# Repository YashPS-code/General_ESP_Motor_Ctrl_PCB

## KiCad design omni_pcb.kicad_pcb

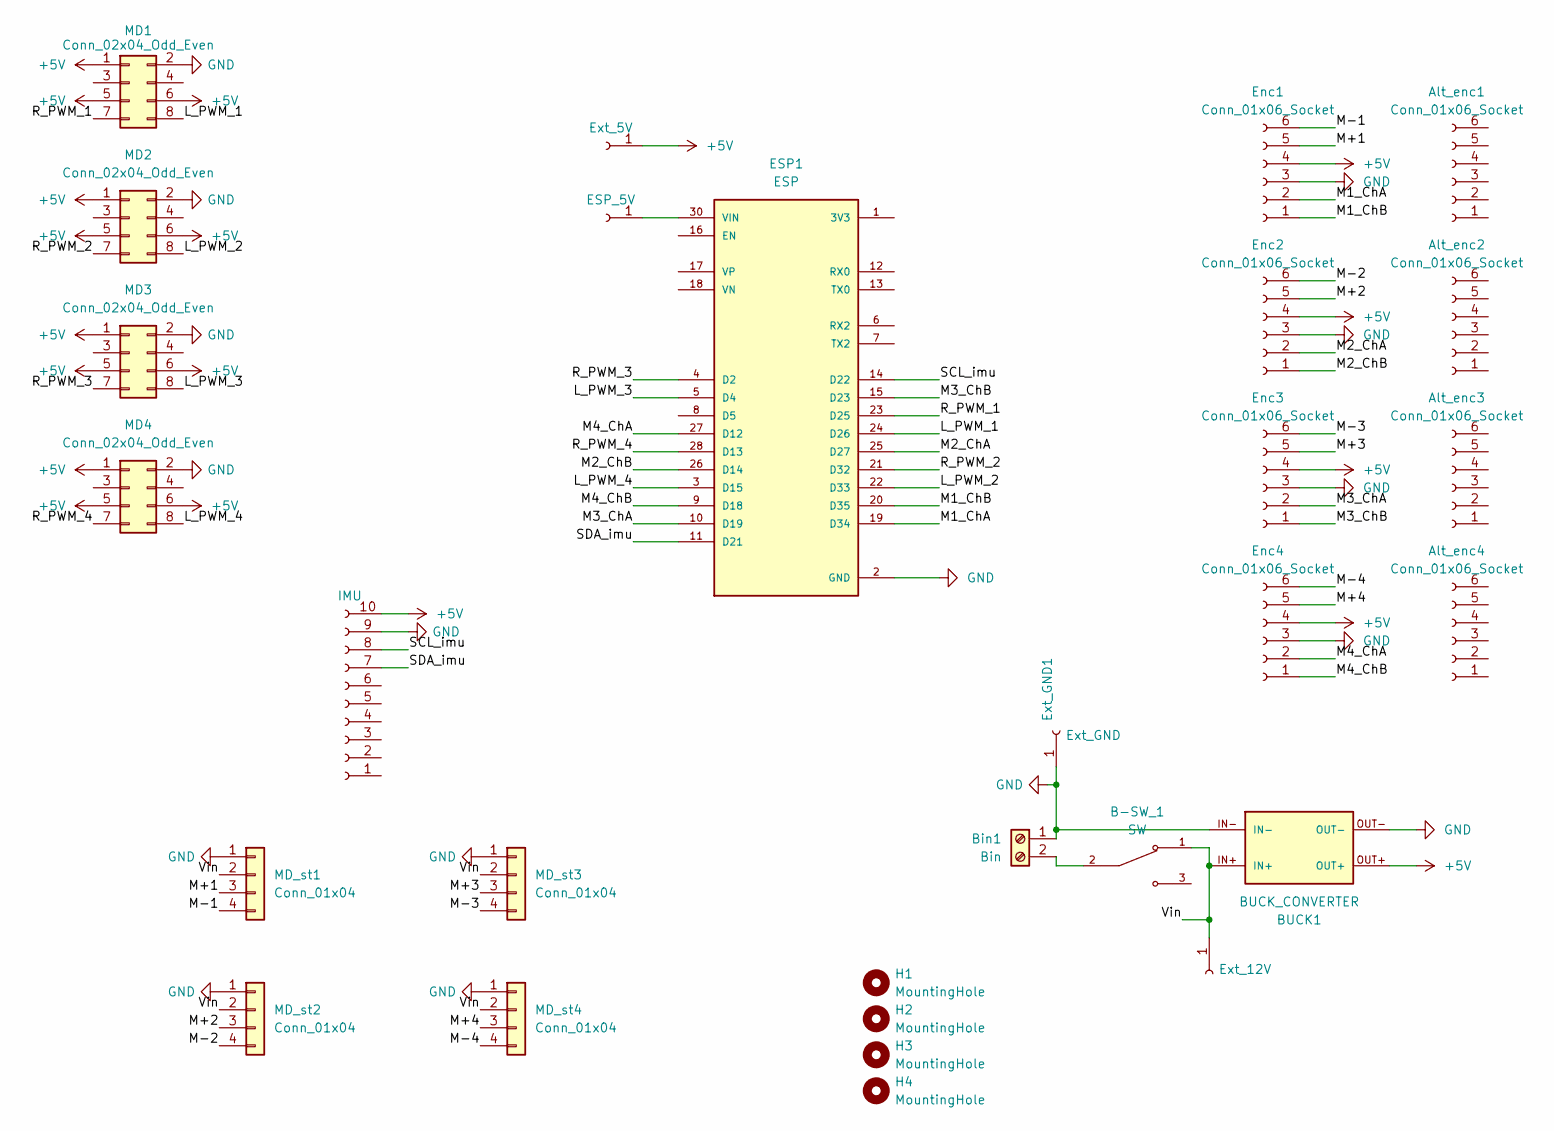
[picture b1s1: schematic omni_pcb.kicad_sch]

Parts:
Alt_enc1, Alt_enc2, Alt_enc3, Alt_enc4: Conn_01x06_Socket; JST_XH_B6B-XH-A_1x06_P2.50mm_Vertical
B-SW_1: SW; SW_100SP1T1B4M2QE; PARTREV E
BUCK1: BUCK_CONVERTER; BUCK_CONVERTER_XL4015E1
Bin1: Bin; TerminalBlock_Xinya_XY308-2.54-2P_1x02_P2.54mm_Horizontal
ESP1: ESP; MODULE_ESP32_DEVKIT_V1; PARTREV N/A
ESP_5V1: ESP_5V; SolderWirePad_1x01_SMD_2x4mm
Enc1, Enc2, Enc3, Enc4: Conn_01x06_Socket; JST_XH_B6B-XH-A_1x06_P2.50mm_Vertical
Ext_5V1: Ext_5V; SolderWirePad_1x01_SMD_2x4mm
Ext_12V1: Ext_12V; SolderWirePad_1x01_SMD_3x6mm
Ext_GND1: Ext_GND; SolderWirePad_1x01_SMD_3x6mm
H1, H2, H3, H4: MountingHole; MountingHole_2.5mm
IMU1: IMU; PinSocket_1x10_P2.54mm_Vertical
MD1, MD2, MD3, MD4: Conn_02x04_Odd_Even; PinSocket_2x04_P2.54mm_Vertical
MD_st1, MD_st2, MD_st3, MD_st4: Conn_01x04; JST_XH_B4B-XH-A_1x04_P2.50mm_Vertical

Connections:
+5V: BUCK1.OUT+, Enc1.4, Enc2.4, Enc3.4, Enc4.4, Ext_5V1.1, IMU1.10, MD1.1, MD1.5, MD1.6, MD2.1, MD2.5, MD2.6, MD3.1, MD3.5, MD3.6, MD4.1, MD4.5, MD4.6
/L_PWM_1: ESP1.24 (D26), MD1.8
/L_PWM_2: ESP1.22 (D33), MD2.8
/L_PWM_3: ESP1.5 (D4), MD3.8
/L_PWM_4: ESP1.3 (D15), MD4.8
/M1_ChA: ESP1.19 (D34), Enc1.2
/M1_ChB: ESP1.20 (D35), Enc1.1
/M2_ChA: ESP1.25 (D27), Enc2.2
/M2_ChB: ESP1.26 (D14), Enc2.1
/M3_ChA: ESP1.10 (D19), Enc3.2
/M3_ChB: ESP1.15 (D23), Enc3.1
/M4_ChA: ESP1.27 (D12), Enc4.2
/M4_ChB: ESP1.9 (D18), Enc4.1
/M+1: Enc1.5, MD_st1.3
/M+2: Enc2.5, MD_st2.3
/M+3: Enc3.5, MD_st3.3
/M+4: Enc4.5, MD_st4.3
/M-1: Enc1.6, MD_st1.4
/M-2: Enc2.6, MD_st2.4
/M-3: Enc3.6, MD_st3.4
/M-4: Enc4.6, MD_st4.4
/R_PWM_1: ESP1.23 (D25), MD1.7
/R_PWM_2: ESP1.21 (D32), MD2.7
/R_PWM_3: ESP1.4 (D2), MD3.7
/R_PWM_4: ESP1.28 (D13), MD4.7
/SCL_imu: ESP1.14 (D22), IMU1.8
/SDA_imu: ESP1.11 (D21), IMU1.7
/Vin: B-SW_1.1, BUCK1.IN+, Ext_12V1.1, MD_st1.2, MD_st2.2, MD_st3.2, MD_st4.2
GND: BUCK1.IN-, BUCK1.OUT-, Bin1.1, ESP1.2 (GND), ESP1.29 (GND), Enc1.3, Enc2.3, Enc3.3, Enc4.3, Ext_GND1.1, IMU1.9, MD1.2, MD2.2, MD3.2, MD4.2, MD_st1.1, MD_st2.1, MD_st3.1, MD_st4.1
unnamed: B-SW_1.2, Bin1.2
unnamed: ESP1.30 (VIN), ESP_5V1.1

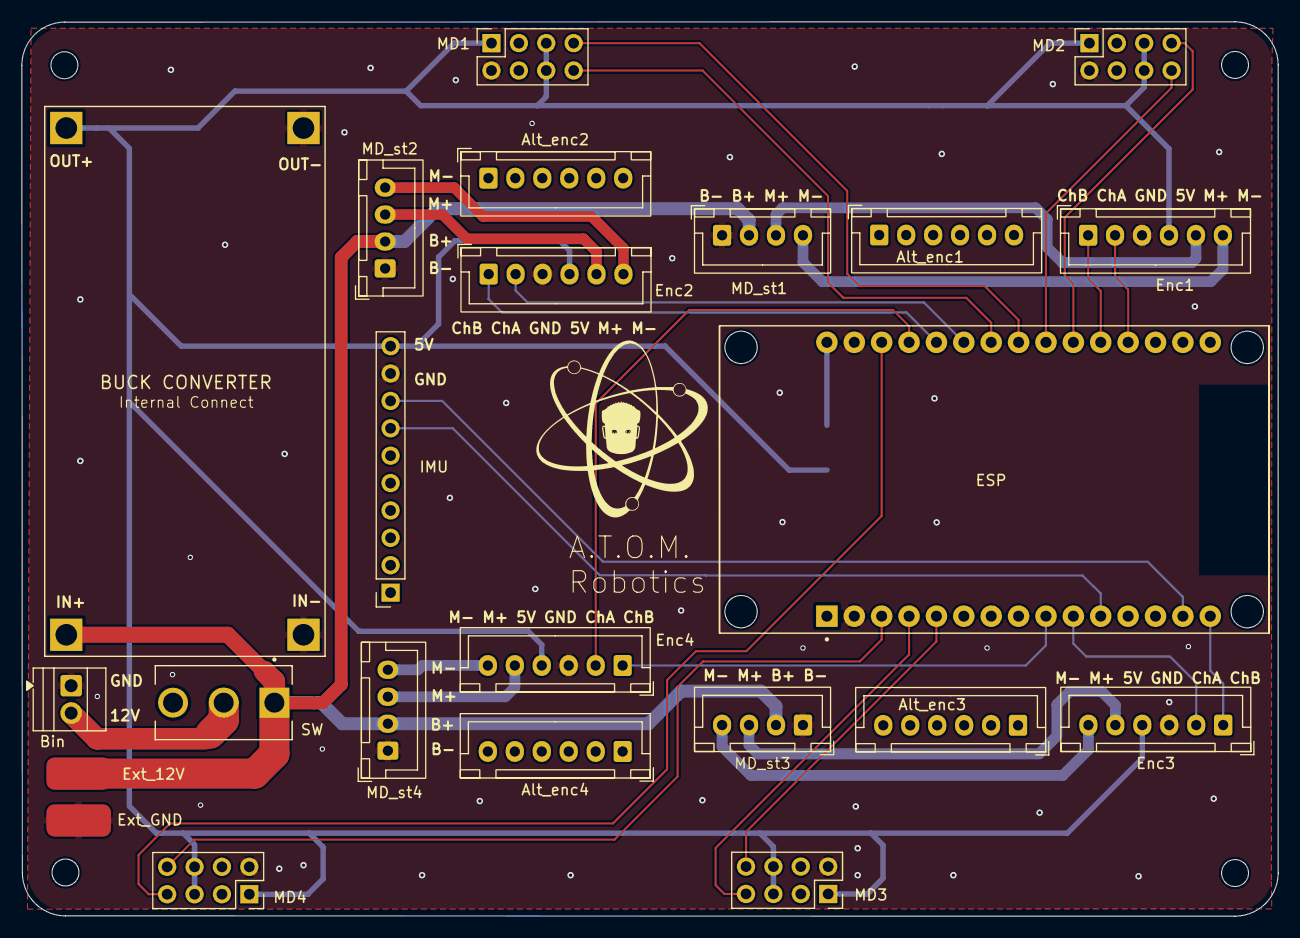
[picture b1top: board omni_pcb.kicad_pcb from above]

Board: 2 copper layers, 116.5 x 82.9 mm, 30 parts (0 on the bottom side), 31 nets.

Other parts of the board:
atom: LOGO; atom_logo_20x20mm

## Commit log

2026-04-13 PCB layout
2026-04-13 Remove unwanted file
2026-05-07 traces
2026-05-08 pcb final
2026-05-09 pin changes
2026-05-11 order change
2026-05-18 Add images to README.md
